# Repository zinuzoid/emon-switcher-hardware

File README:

# Electric Monitoring and Switcher v0.1

This is a hardware capable of monitor household AC voltage and current which will be pass to RaspberryPi-Zero2W. It has 2 relay outputs and 2 LEDs.

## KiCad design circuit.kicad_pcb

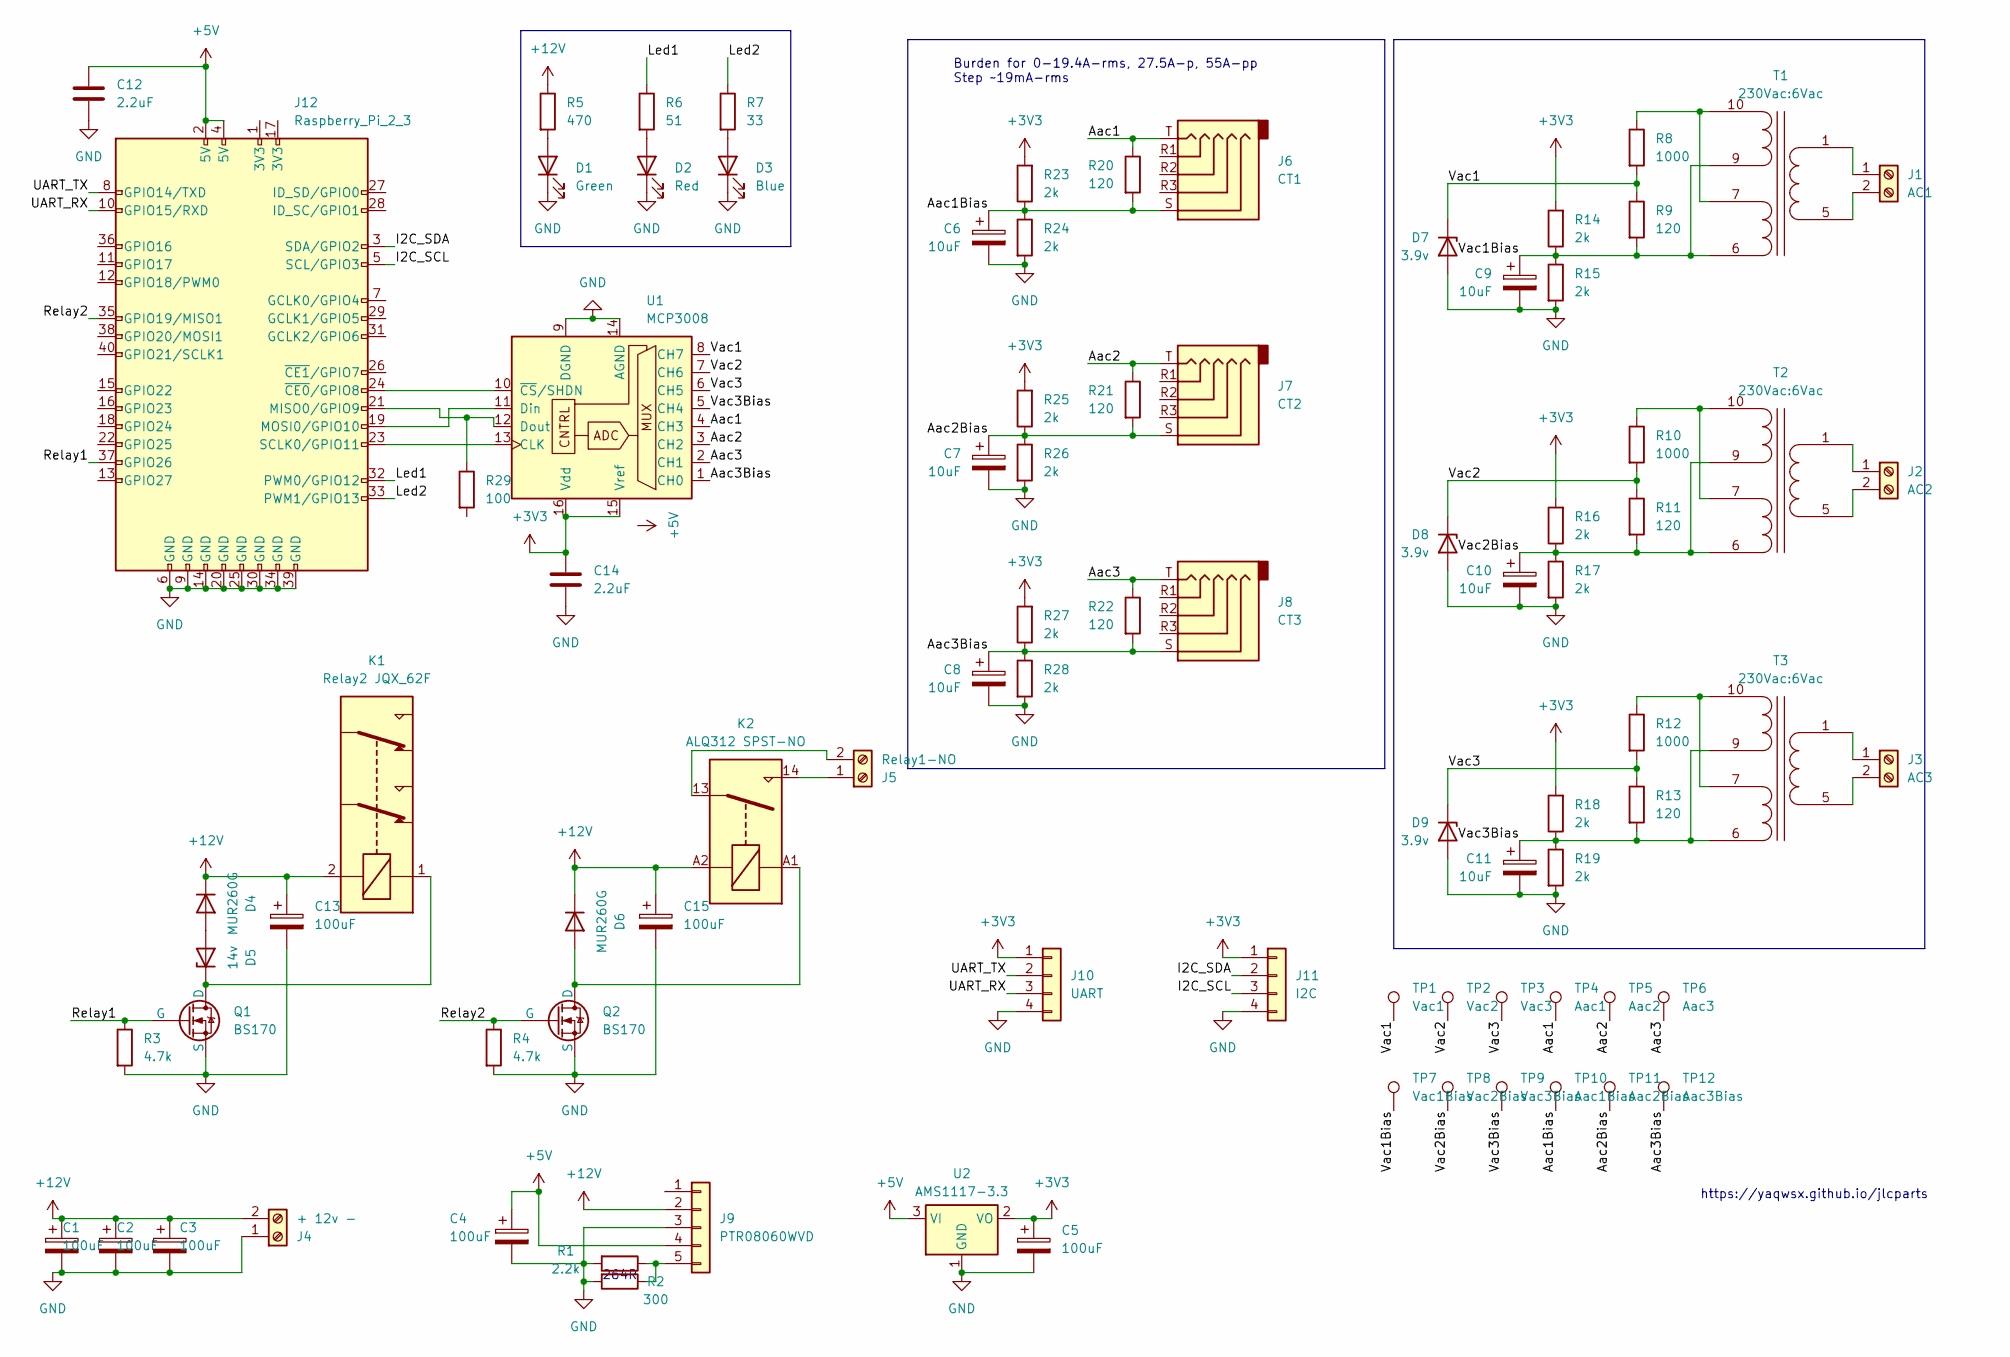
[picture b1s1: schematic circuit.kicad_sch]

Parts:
C1, C2, C3, C4, C5, C13, C15: 100uF; C_1206_3216Metric; JLCPCB C15008
C6, C7, C8, C9, C10, C11: 10uF; C_0805_2012Metric; JLCPCB C15850
C12, C14: 2.2uF; C_1206_3216Metric; JLCPCB C50254
D1: Green; LED_0805_2012Metric; JLCPCB C2297
D2: Red; LED_0805_2012Metric; JLCPCB C84256
D3: Blue; LED_0805_2012Metric; JLCPCB C34499
D4, D6: MUR260G; D_DO-41_SOD81_P12.70mm_Horizontal
D5: 14v; D_DO-15_P15.24mm_Horizontal
D7, D8, D9: 3.9v; D_DO-15_P15.24mm_Horizontal
J1: AC1; KF38S-8.25-2P; JLCPCB C707644
J2: AC2; KF38S-8.25-2P; JLCPCB C707644
J3: AC3; KF38S-8.25-2P; JLCPCB C707644
J4: + 12v -; KF38S-8.25-2P; JLCPCB C707644
J5: Relay1-NO; KF38S-8.25-2P; JLCPCB C707644
J6: CT1; Jack_3.5mm-ACJS-NV35-5
J7: CT2; Jack_3.5mm-ACJS-NV35-5
J8: CT3; Jack_3.5mm-ACJS-NV35-5
J9: PTR08060WVD
J10: UART; PinHeader_1x04_P2.54mm_Vertical
J11: I2C; PinHeader_1x04_P2.54mm_Vertical
J12: Raspberry_Pi_2_3; PinSocket_2x20_P2.54mm_Vertical_Reverse
K1: Relay2 JQX_62F; KF38S-8.25-2P; JLCPCB C707644
K2: ALQ312 SPST-NO; Relay-ALQ
Q1, Q2: BS170; TO-92
R1: 2.2k; R_0805_2012Metric; JLCPCB C17520
R2: 300; R_0805_2012Metric; JLCPCB C17617
R3, R4: 4.7k; R_0805_2012Metric; JLCPCB C17673
R5: 470; LED_0805_2012Metric; JLCPCB C17710
R6: 51; LED_0805_2012Metric; JLCPCB C17738
R7: 33; LED_0805_2012Metric; JLCPCB C17634
R8, R10, R12: 1000; R_1206_3216Metric; JLCPCB C4410
R9, R11, R13: 120; R_1206_3216Metric; JLCPCB C17909
R14, R15, R16, R17, R18, R19, R23, R24, R25, R26, R27, R28: 2k; R_0805_2012Metric; JLCPCB C17604
R20, R21, R22: 120; R_0805_2012Metric; JLCPCB C17437
R29: 100; R_0805_2012Metric; JLCPCB C17408
T1, T2, T3: 230Vac:6Vac; Myrra PCB Transformer
TP1: Vac1; TestPoint_Pad_D1.0mm
TP2: Vac2; TestPoint_Pad_D1.0mm
TP3: Vac3; TestPoint_Pad_D1.0mm
TP4: Aac1; TestPoint_Pad_D1.0mm
TP5: Aac2; TestPoint_Pad_D1.0mm
TP6: Aac3; TestPoint_Pad_D1.0mm
TP7: Vac1Bias; TestPoint_Pad_D1.0mm
TP8: Vac2Bias; TestPoint_Pad_D1.0mm
TP9: Vac3Bias; TestPoint_Pad_D1.0mm
TP10: Aac1Bias; TestPoint_Pad_D1.0mm
TP11: Aac2Bias; TestPoint_Pad_D1.0mm
TP12: Aac3Bias; TestPoint_Pad_D1.0mm
U1: MCP3008; DIP-16_W7.62mm
U2: AMS1117-3.3; SOT-223-3_TabPin2; JLCPCB C6186

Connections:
+3V3: C5.1, C14.1, J10.1, J11.1, R14.2, R16.2, R18.2, R23.2, R25.2, R27.2, U1.15 (Vref), U1.16 (Vdd), U2.2 (VO)
+5V: C4.1, C12.1, J9.4, J12.2 (5V), J12.4 (5V), U2.3 (VI)
+12V: C1.1, C2.1, C3.1, C13.1, C15.1, D4.1 (K), D6.1 (K), J4.2, J9.2, K1.2, K2.A2, R5.1
/Aac1: J6.T, R20.1, TP4.1, U1.4 (CH3)
/Aac1Bias: C6.1, J6.S, R20.2, R23.1, R24.1, TP10.1
/Aac2: J7.T, R21.1, TP5.1, U1.3 (CH2)
/Aac2Bias: C7.1, J7.S, R21.2, R25.1, R26.1, TP11.1
/Aac3: J8.T, R22.1, TP6.1, U1.2 (CH1)
/Aac3Bias: C8.1, J8.S, R22.2, R27.1, R28.1, TP12.1, U1.1 (CH0)
/I2C_SCL: J11.3, J12.5 (SCL/GPIO3)
/I2C_SDA: J11.2, J12.3 (SDA/GPIO2)
/Led1: J12.32 (PWM0/GPIO12), R6.1
/Led2: J12.33 (PWM1/GPIO13), R7.1
/Relay1: J12.37 (GPIO26), Q1.2 (G), R3.1
/Relay2: J12.35 (GPIO19/MISO1), Q2.2 (G), R4.1
/UART_RX: J10.3, J12.10 (GPIO15/RXD)
/UART_TX: J10.2, J12.8 (GPIO14/TXD)
/Vac1: D7.1 (K), R8.2, R9.1, TP1.1, U1.8 (CH7)
/Vac1Bias: C9.1, R9.2, R14.1, R15.1, T1.6 (SA), T1.9 (SC), TP7.1
/Vac2: D8.1 (K), R10.2, R11.1, TP2.1, U1.7 (CH6)
/Vac2Bias: C10.1, R11.2, R16.1, R17.1, T2.6 (SA), T2.9 (SC), TP8.1
/Vac3: D9.1 (K), R12.2, R13.1, TP3.1, U1.6 (CH5)
/Vac3Bias: C11.1, R13.2, R18.1, R19.1, T3.6 (SA), T3.9 (SC), TP9.1, U1.5 (CH4)
GND: C1.2, C2.2, C3.2, C4.2, C5.2, C6.2, C7.2, C8.2, C9.2, C10.2, C11.2, C12.2, C13.2, C14.2, C15.2, D1.1 (K), D2.1 (K), D3.1 (K), D7.2 (A), D8.2 (A), D9.2 (A), J4.1, J9.3, J10.4, J11.4, J12.6 (GND), J12.9 (GND), J12.14 (GND), J12.20 (GND), J12.25 (GND), J12.30 (GND), J12.34 (GND), J12.39 (GND), Q1.3 (S), Q2.3 (S), R1.2, R2.2, R3.2, R4.2, R15.2, R17.2, R19.2, R24.2, R26.2, R28.2, U1.9 (DGND), U1.14 (AGND), U2.1 (GND)
unnamed: D1.2 (A), R5.2
unnamed: D2.2 (A), R6.2
unnamed: D3.2 (A), R7.2
unnamed: D4.2 (A), D5.2 (A)
unnamed: D5.1 (K), K1.1, Q1.1 (D)
unnamed: D6.2 (A), K2.A1, Q2.1 (D)
unnamed: J1.1, T1.1 (AB)
unnamed: J1.2, T1.5 (AA)
unnamed: J2.1, T2.1 (AB)
unnamed: J2.2, T2.5 (AA)
unnamed: J3.1, T3.1 (AB)
unnamed: J3.2, T3.5 (AA)
unnamed: J5.1, K2.14
unnamed: J5.2, K2.13
unnamed: J9.5, R1.1, R2.1
unnamed: J12.21 (MISO0/GPIO9), R29.1, U1.12 (Dout)
unnamed: J12.19 (MOSI0/GPIO10), U1.11 (Din)
unnamed: J12.23 (SCLK0/GPIO11), U1.13 (CLK)
unnamed: J12.24 (~CE0/GPIO8), U1.10 (~CS/SHDN)
unnamed: R8.1, T1.7 (SB), T1.10 (SD)
unnamed: R10.1, T2.7 (SB), T2.10 (SD)
unnamed: R12.1, T3.7 (SB), T3.10 (SD)

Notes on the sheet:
https://yaqwsx.github.io/jlcparts
Burden for 0-19.4A-rms, 27.5A-p, 55A-pp Step ~19mA-rms
264R

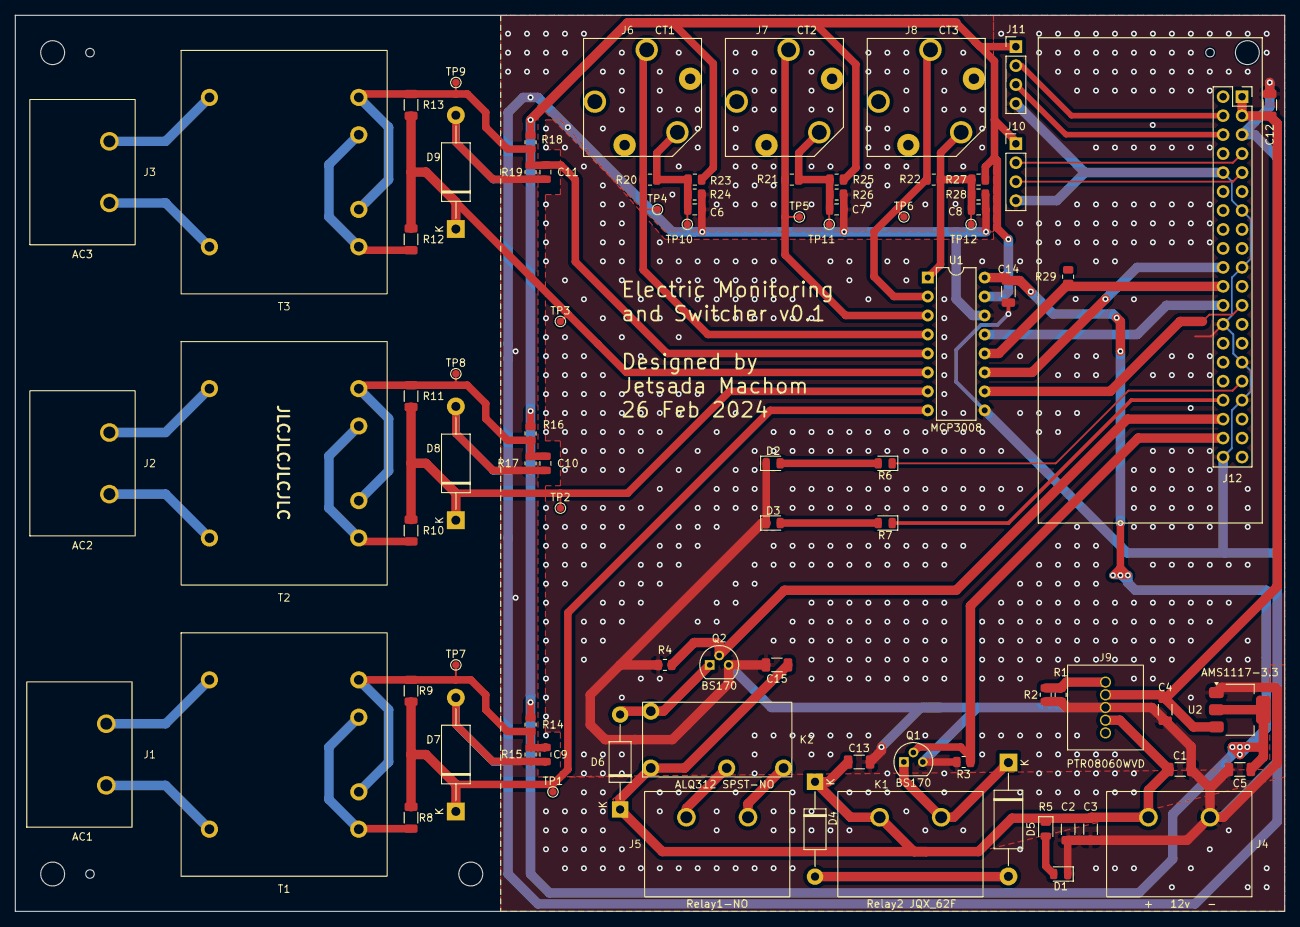
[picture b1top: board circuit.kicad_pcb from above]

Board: 2 copper layers, 170.0 x 120.0 mm, 86 parts (0 on the bottom side), 46 nets.
